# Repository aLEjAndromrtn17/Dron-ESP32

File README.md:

# Dron-ESP32
Aquí encontraras todos los archivos de creación para realizar el proyecto

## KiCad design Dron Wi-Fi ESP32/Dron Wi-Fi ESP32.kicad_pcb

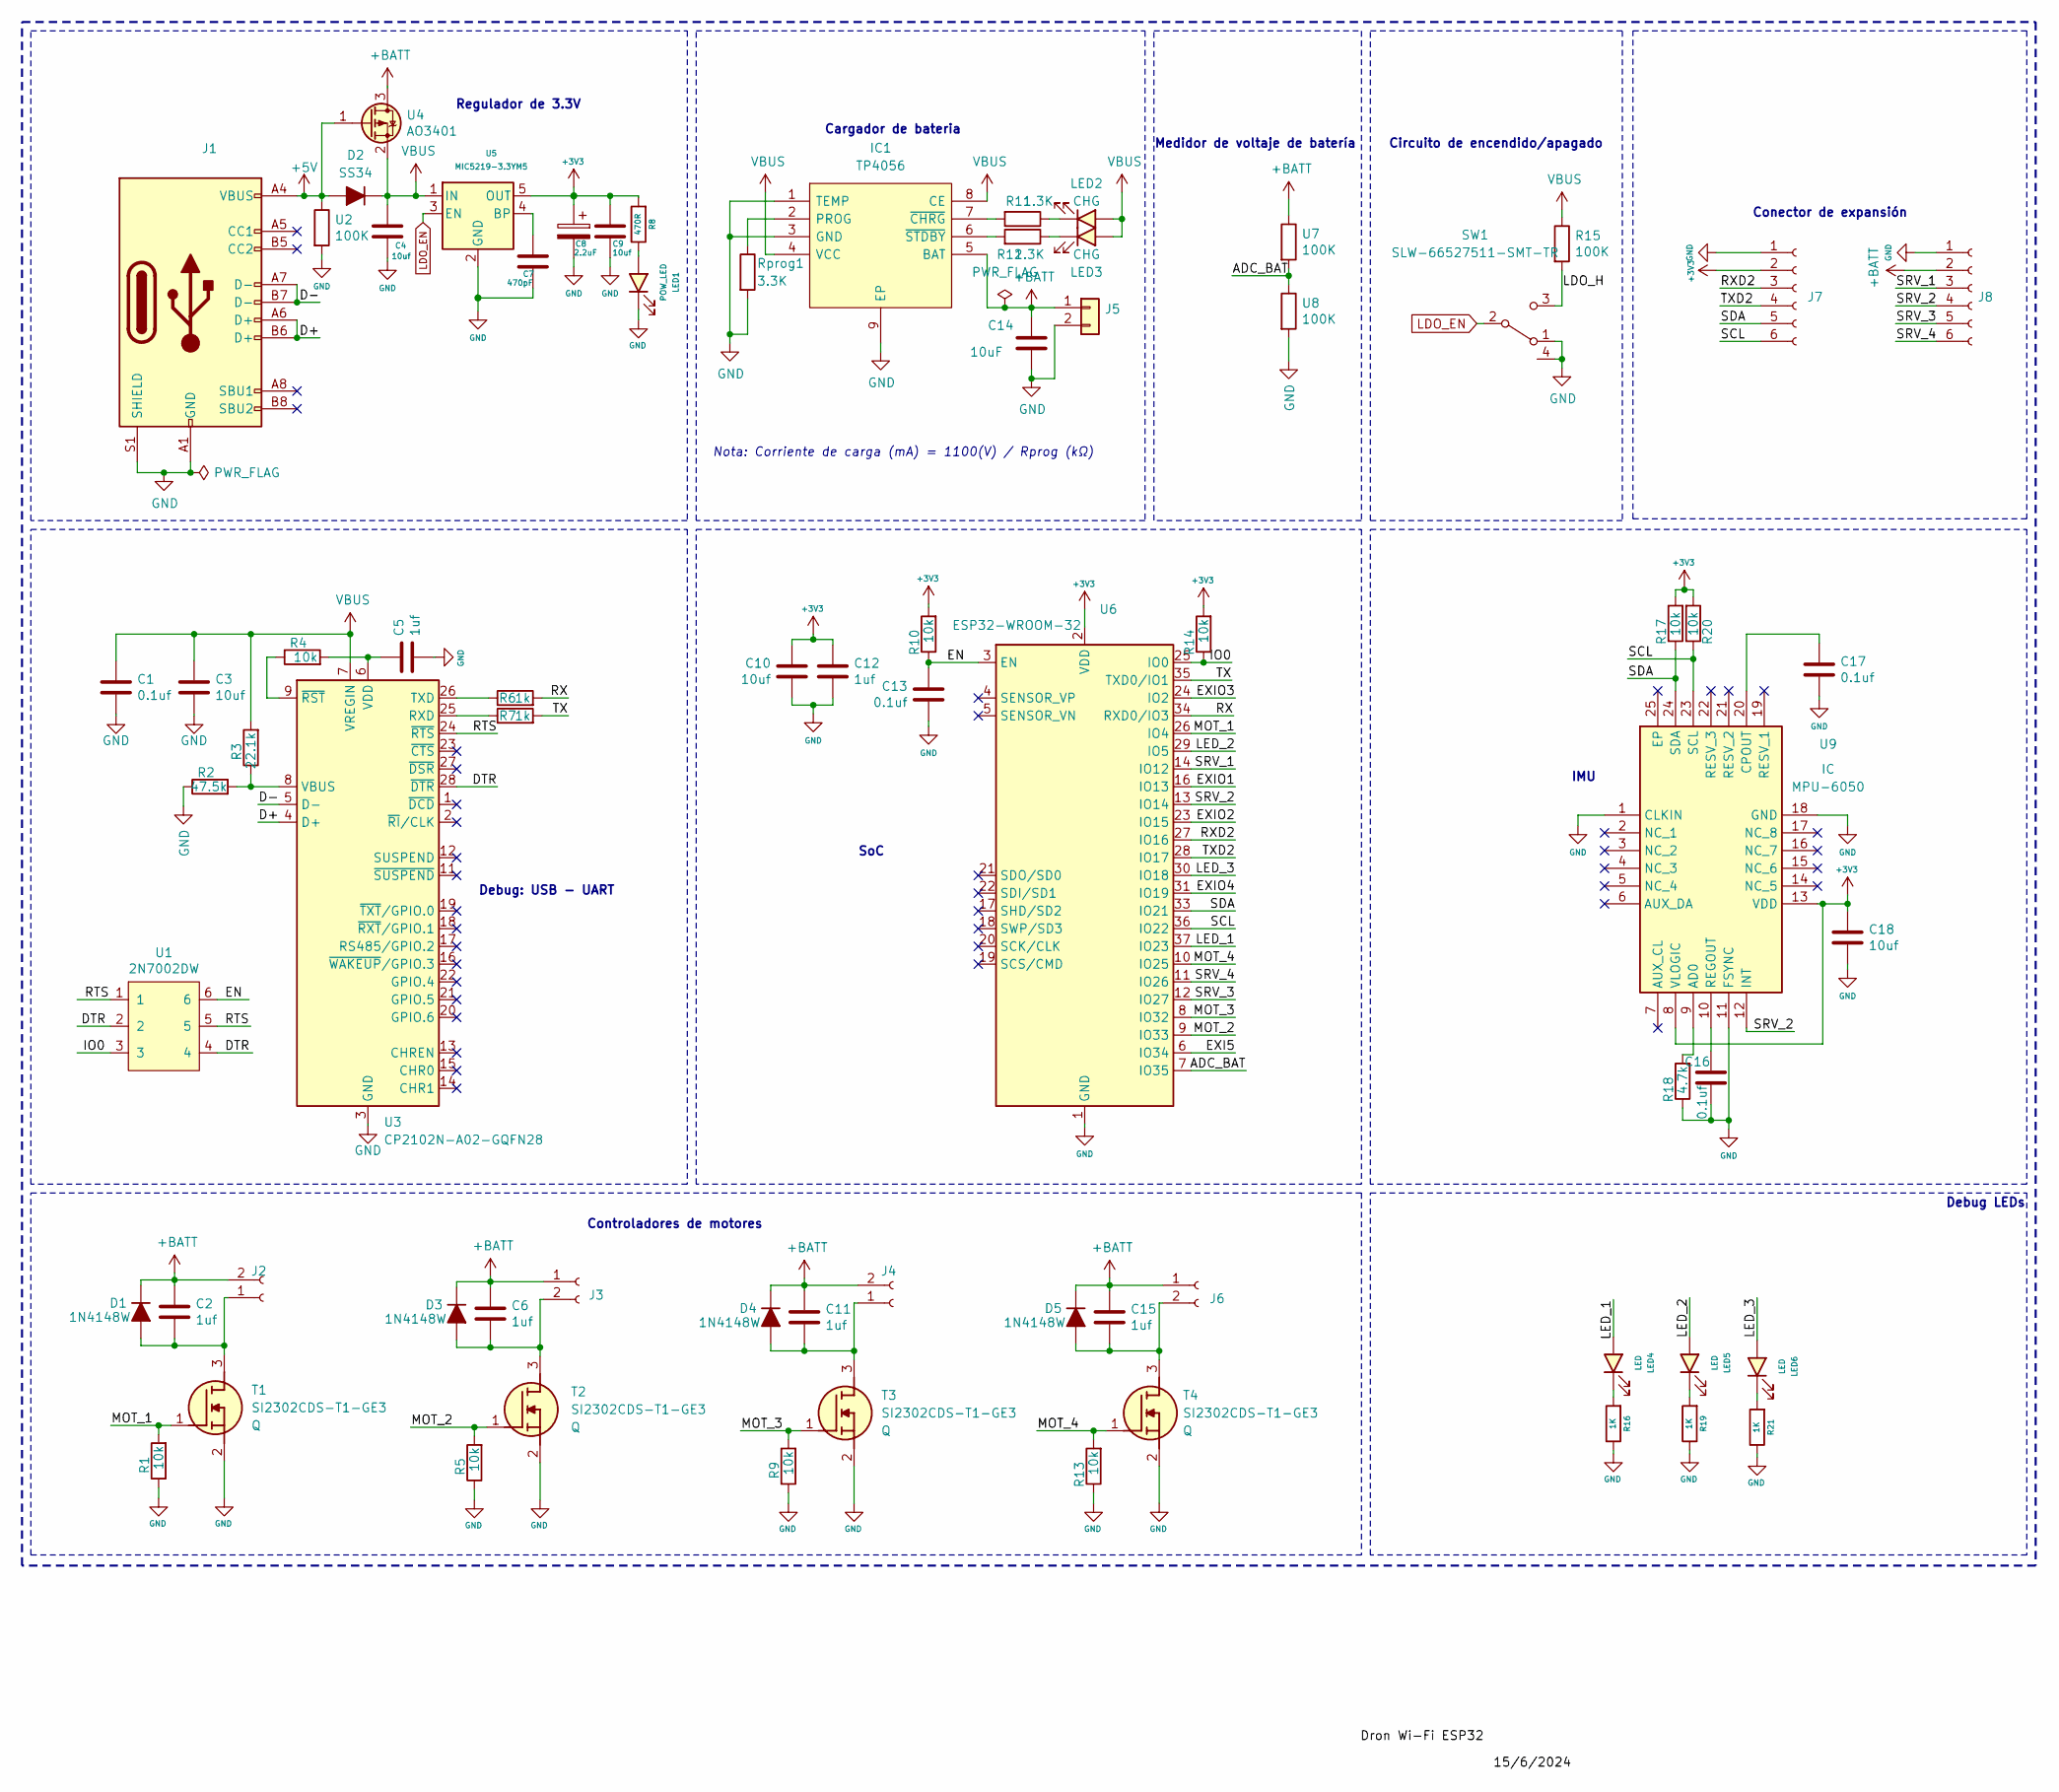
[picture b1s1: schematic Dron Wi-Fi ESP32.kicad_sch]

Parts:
C1, C13, C16, C17: 0.1uf; C_0603_1608Metric
C2, C5, C6, C11, C12, C15: 1uf; C_0603_1608Metric
C3, C4, C9, C10, C18: 10uf; C_0603_1608Metric
C7: 470pF; C_0603_1608Metric
C8: 2.2uF; C_0805_2012Metric
C14: 10uF; C_0603_1608Metric
D1, D3, D4, D5: 1N4148W; D_SOD-323
D2: SS34; D_SMA
IC1: TP4056; SOIC127P600X175-9N; Manufacturer_Part_Number TP4056-42-ESOP8
J1: USB_C_Receptacle_USB2.0; USB_C_Receptacle_HRO_TYPE-C-31-M-12
J2, J3, J4, J6: Conn_01x02_Female; JST_GH_SM02B-GHS-TB_1x02-1MP_P1.25mm_Horizontal
J5: B2B-PH-SM4-TB(LF)(SN); JST_PH_B2B-PH-SM4-TB_1x02-1MP_P2.00mm_Vertical
J7, J8: Conn_01x06_Female; PinHeader_1x06_P2.54mm_Vertical
LED1: POW_LED; LED_0603_1608Metric
LED2, LED3: CHG; LED_0603_1608Metric
LED4, LED5, LED6: LED; LED_0603_1608Metric
R1, R4, R5, R9, R10, R13, R14, R17, R20: 10k; R_0603_1608Metric
R2: 47.5k; R_0603_1608Metric
R3: 22.1k; R_0603_1608Metric
R6, R7: 1k; R_0603_1608Metric
R8: 470R; R_0603_1608Metric
R11, R12: 1.3K; R_0603_1608Metric
R15: 100K; R_0603_1608Metric
R16, R19, R21: 1K; R_0603_1608Metric
R18: 4.7k; R_0603_1608Metric
Rprog1: 3.3K; R_0603_1608Metric
SW1: SLW-66527511-SMT-TR; SLW66527511SMTTR
T1, T2, T3, T4: SI2302CDS-T1-GE3; SOT95P237X112-3N; Mouser Part Number 781-SI2302DS
U1: 2N7002DW; SOT-363_SC-70-6
U2, U7, U8: 100K; R_0603_1608Metric
U3: CP2102N-A02-GQFN28; QFN-28-1EP_5x5mm_P0.5mm_EP3.35x3.35mm
U4: AO3401; SOT-23
U5: MIC5219-3.3YM5; SOT-23-5
U6: ESP32-WROOM-32
U9: MPU-6050; MPU6050; Mouser Part Number 410-MPU-6050

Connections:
+3V3: C8.1, C9.1, C10.1, C12.1, C18.1, J7.2, R8.2, R10.2, R14.2, R17.2, R20.2, U5.5 (OUT), U6.2 (VDD), U9.8 (VLOGIC), U9.13 (VDD)
+5V: D2.2 (A), J1.A4 (VBUS), J1.A9 (VBUS), J1.B4 (VBUS), J1.B9 (VBUS), U2.1, U4.1 (G)
+BATT: C2.1, C6.1, C11.1, C14.1, C15.1, D1.1 (K), D3.1 (K), D4.1 (K), D5.1 (K), IC1.5 (BAT), J2.2, J3.1, J4.2, J5.1, J6.1, J8.2, U4.3 (D), U7.1
/ADC_BAT: U6.7 (IO35), U7.2, U8.1
/D+: J1.A6 (D+), J1.B6 (D+), U3.4 (D+)
/D-: J1.A7 (D-), J1.B7 (D-), U3.5 (D-)
/DTR: U1.2, U1.4, U3.28 (~DTR)
/EN: C13.1, R10.1, U1.6, U6.3 (EN)
/EXI5: U6.6 (IO34)
/EXIO1: U6.16 (IO13)
/EXIO2: U6.23 (IO15)
/EXIO3: U6.24 (IO2)
/EXIO4: U6.31 (IO19)
/IO0: R14.1, U1.3, U6.25 (IO0)
/LDO_H: R15.2, SW1.3 (C)
/LED_1: LED4.2 (A), U6.37 (IO23)
/LED_2: LED5.2 (A), U6.29 (IO5)
/LED_3: LED6.2 (A), U6.30 (IO18)
/MOT_1: R1.2, T1.1 (G), U6.26 (IO4)
/MOT_2: R5.2, T2.1 (G), U6.9 (IO33)
/MOT_3: R9.2, T3.1 (G), U6.8 (IO32)
/MOT_4: R13.2, T4.1 (G), U6.10 (IO25)
/RTS: U1.1, U1.5, U3.24 (~RTS)
/RX: R6.2, U6.34 (RXD0/IO3)
/RXD2: J7.3, U6.27 (IO16)
/SCL: J7.6, R20.1, U6.36 (IO22), U9.23 (SCL)
/SDA: J7.5, R17.1, U6.33 (IO21), U9.24 (SDA)
/SRV_1: J8.3, U6.14 (IO12)
/SRV_2: J8.4, U6.13 (IO14), U9.12 (INT)
/SRV_3: J8.5, U6.12 (IO27)
/SRV_4: J8.6, U6.11 (IO26)
/TX: R7.2, U6.35 (TXD0/IO1)
/TXD2: J7.4, U6.28 (IO17)
GND: C1.2, C3.2, C4.2, C5.2, C7.2, C8.2, C9.2, C10.2, C12.2, C13.2, C14.2, C16.2, C17.2, C18.2, IC1.1 (TEMP), IC1.3 (GND), IC1.9 (EP), J1.A1 (GND), J1.A12 (GND), J1.B1 (GND), J1.B12 (GND), J1.S1 (SHIELD), J5.2, J7.1, J8.1, LED1.1 (K), R1.1, R2.1, R5.1, R9.1, R13.1, R16.1, R18.1, R19.1, R21.1, Rprog1.2, SW1.1 (A), SW1.4, T1.2 (S), T2.2 (S), T3.2 (S), T4.2 (S), U2.2, U3.3 (GND), U3.29 (GND), U5.2 (GND), U6.1 (GND), U6.15 (GND), U6.38 (GND), U6.39 (GND), U8.2, U9.1 (CLKIN), U9.11 (FSYNC), U9.18 (GND)
LDO_EN: SW1.2 (B), U5.3 (EN)
unnamed: C2.2, D1.2 (A), J2.1, T1.3 (D)
unnamed: C6.2, D3.2 (A), J3.2, T2.3 (D)
unnamed: C11.2, D4.2 (A), J4.1, T3.3 (D)
unnamed: C15.2, D5.2 (A), J6.2, T4.3 (D)
unnamed: IC1.2 (PROG), Rprog1.1
unnamed: IC1.7 (~CHRG), R11.2
unnamed: IC1.6 (~STDBY), R12.2
unnamed: LED1.2 (A), R8.1
unnamed: LED2.1 (K), R11.1
unnamed: LED3.1 (K), R12.1
unnamed: LED4.1 (K), R16.2
unnamed: LED5.1 (K), R19.2
unnamed: LED6.1 (K), R21.2
unnamed: R7.1, U3.25 (RXD)
unnamed: R6.1, U3.26 (TXD)
unnamed: R2.2, R3.1, U3.8 (VBUS)
unnamed: C5.1, R4.2, U3.6 (VDD)
unnamed: R4.1, U3.9 (~RST)
unnamed: C7.1, U5.4 (BP)
unnamed: R18.2, U9.9 (AD0)
unnamed: C17.1, U9.20 (CPOUT)
unnamed: C16.1, U9.10 (REGOUT)
VBUS: C1.1, C3.1, C4.1, D2.1 (K), IC1.4 (VCC), IC1.8 (CE), LED2.2 (A), LED3.2 (A), R3.2, R15.1, U3.7 (VREGIN), U4.2 (S), U5.1 (IN)

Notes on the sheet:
Debug: USB - UART
SoC
Circuito de encendido/apagado
Conector de expansión
Medidor de voltaje de batería
Nota: Corriente de carga (mA) = 1100(V) / Rprog (kΩ)
Debug LEDs
Controladores de motores
Cargador de bateria
Regulador de 3.3V
IMU

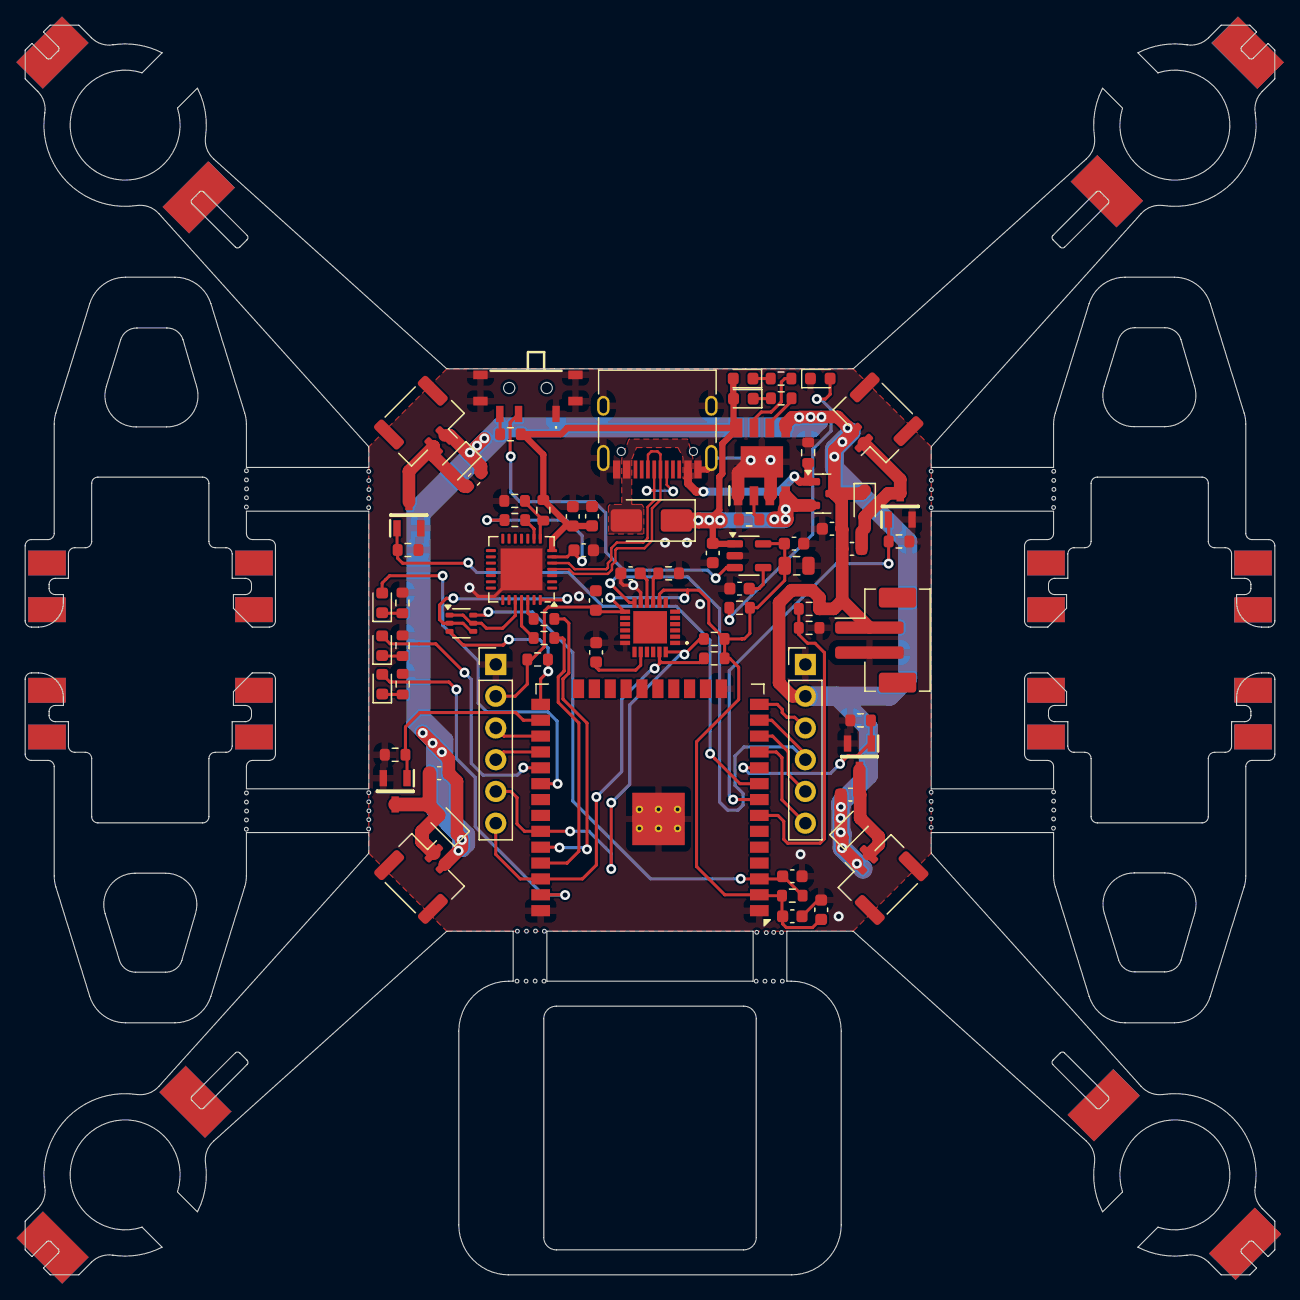
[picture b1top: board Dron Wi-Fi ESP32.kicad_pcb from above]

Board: 2 copper layers, 100.0 x 100.0 mm, 74 parts (0 on the bottom side), 53 nets.
